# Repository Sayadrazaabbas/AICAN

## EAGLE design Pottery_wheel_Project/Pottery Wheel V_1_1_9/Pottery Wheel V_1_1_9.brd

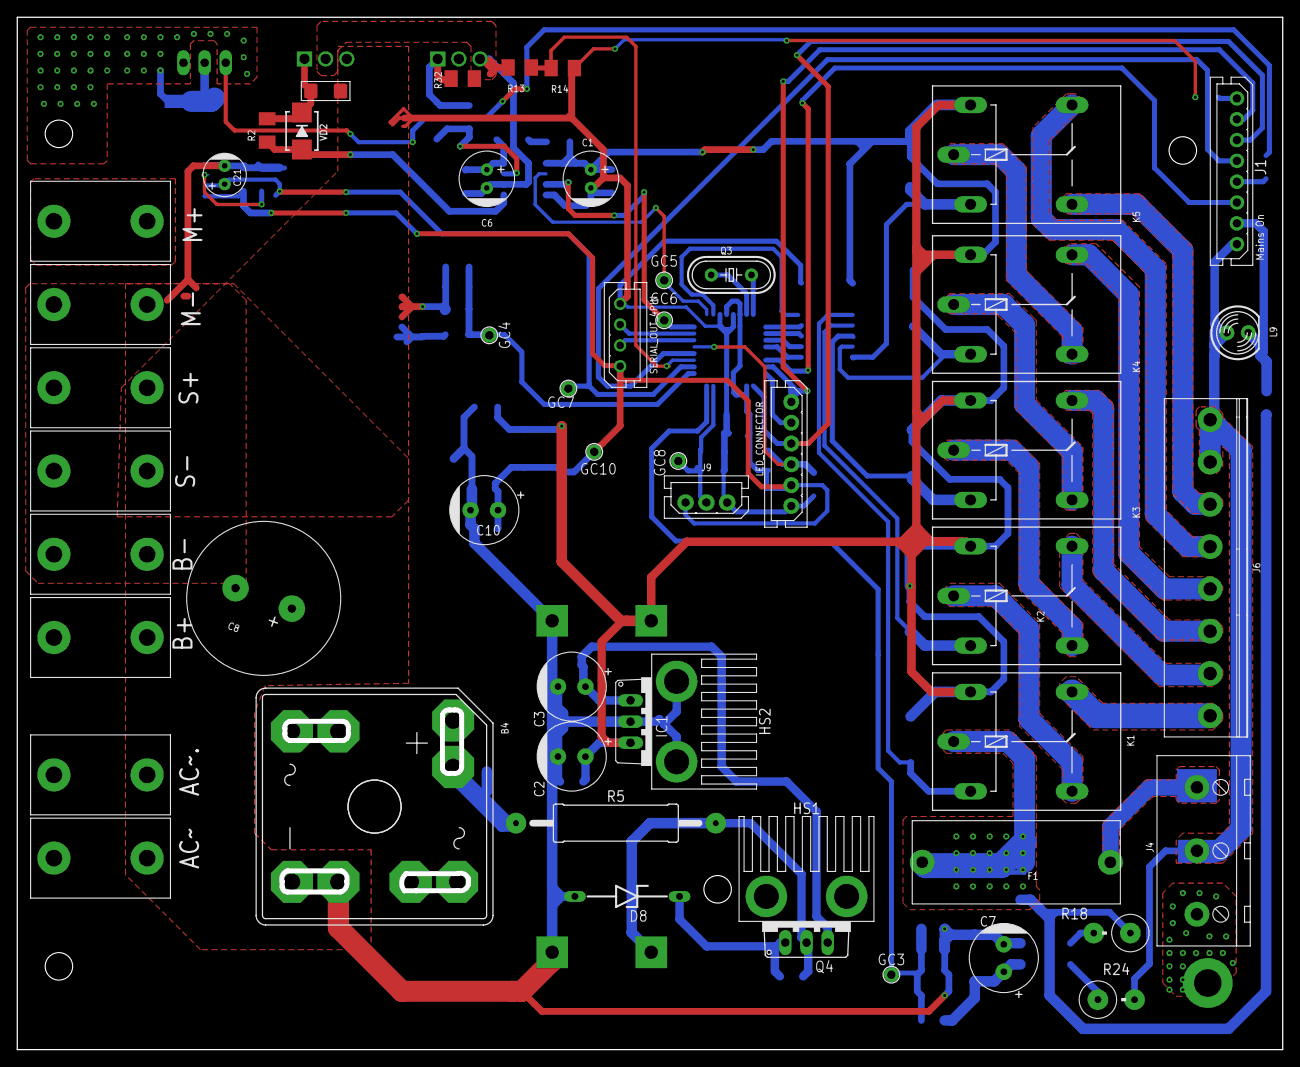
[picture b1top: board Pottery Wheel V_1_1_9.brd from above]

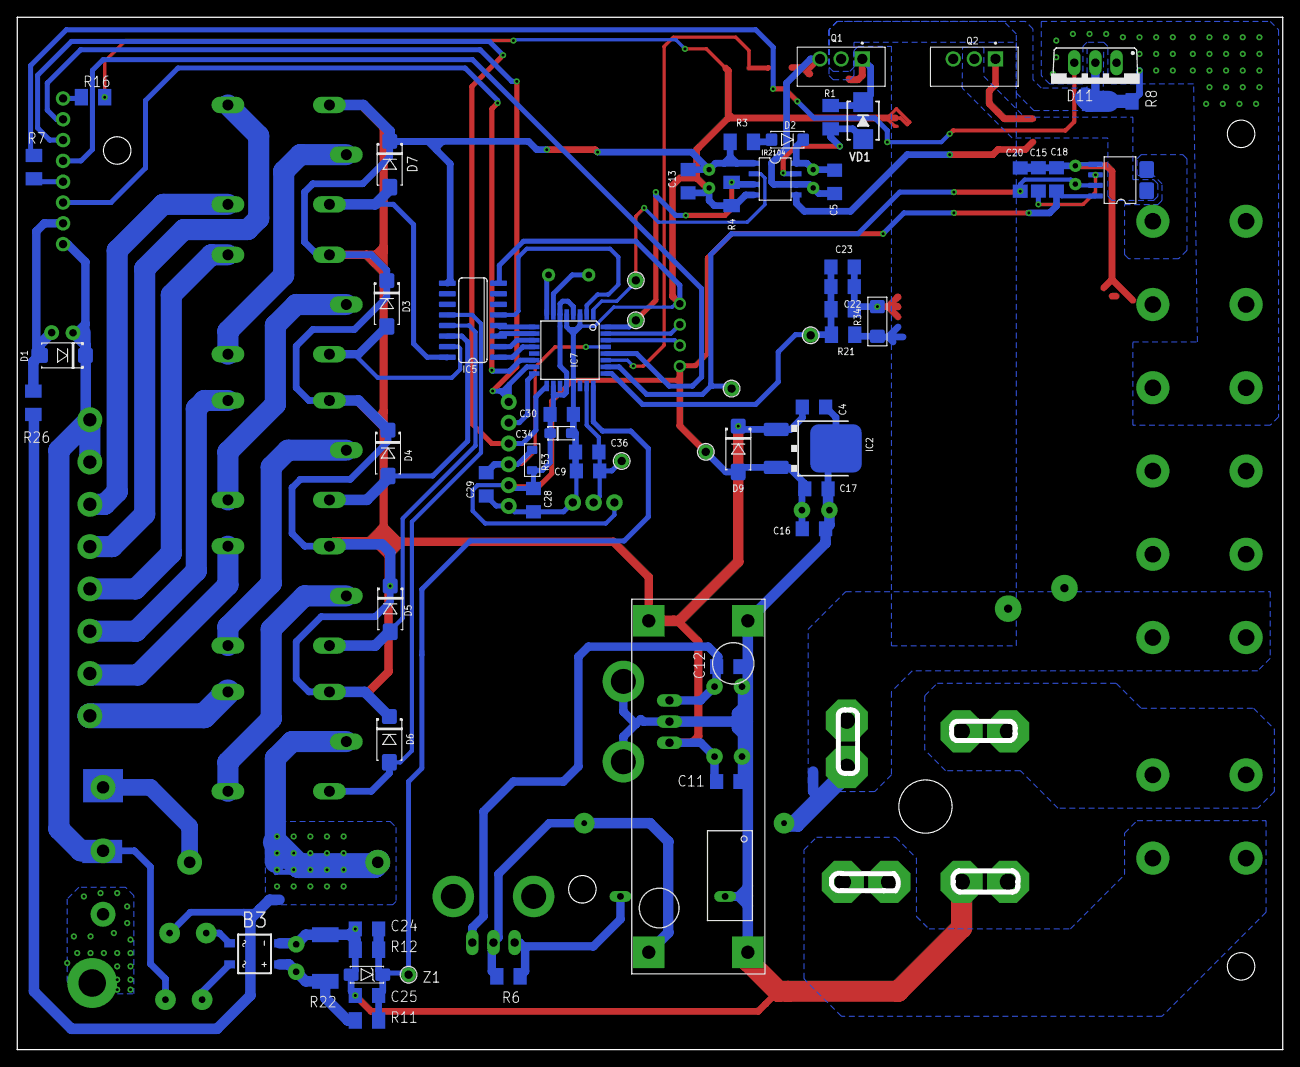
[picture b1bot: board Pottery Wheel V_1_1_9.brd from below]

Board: 2 copper layers, 151.6 x 123.6 mm, 107 parts (55 on the bottom side), 65 nets.

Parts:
AC~, AC~.: 1-PIN_9.6
B3: B1S; MBS
B4: KPC3510; B25A-
B+: 1-PIN_9.6
B-: 1-PIN_9.6
C1, C6: 10uf; C_6_V
C2, C3: DNP; C_8_V
C4, C5, C13, C15, C17, C36: 0.1uf; C1206
C7: 10uf/450v; C_8_V
C8: 4700uf/50V; C_19MM
C9, C16, C18, C20: 1uf; C1206
C10: 10uf/63v; C_8_V
C11, C12: DNP; C1206
C21: 10uf/63v; C_5_V
C22: .1UF; C1206
C23, C25: 1UF; C1206
C24: 0.1UF; C1206
C28, C29, C30: O.1UF; C1206
C34: DNP; TANT_1206
D1, D3, D4, D5, D6, D7, D9: M7; SMB
D2: 5819; SOD-80
D8: DNP; ZDIO12.5
D11: BYV32; TO220ABS
F1: Fuse Holder Pcb Mount; FH_BOX
GC3, GC4, GC5, GC6, GC7, GC8, GC10: P1-17Y
HS1, HS2: DNP; PI-49
IC1: DNP; TO220V
IC2: M7805; DPAK
IC5: ULN2003; SOIC-16
IC7: MEGA8-AI; TQFP32-08
IC8: ACS712-05B; SO-08
J1: MOLEX_8-PIN
J4: 3-PIN_7.62
J6: 5.08 PBT WHITE Power Connecor; 8-PIN_5.08_PWR
J9: 2.54 3 pin JST; MOLEX_3-PIN
K1, K2, K3, K4, K5: G5LE
L9: Red 5mm; LED_5MM
LED_CONNECTOR: MOLEX_6-PIN
M+: 1-PIN_9.6
M-: 1-PIN_9.6
Q1, Q2: IRF2115; TO254P1054X469X2933-3
Q3: 16MHZ; HC49/S
Q4: DNP; TO220AV
R1, R2, R3: 10E; M1206
R4: 10k; M1206
R5: 10E; RES_2W_L
R6: DNP; M1206
R7, R8, R16: 470E; M1206
R11: 1ME; M1206
R12: 11k; M1206
R13: 5.2k; M1206
R14: 1k; M1206
R15: 10K; 1206
R18, R24: 0E; 2W
R21, R32: 10K; M1206
R22: 200K; R2512
R23: 1K; M1206
R26: 100k; M1206
R34: DNP; 1206
R53: 10K; 0805
S+: 1-PIN_9.6
S-: 1-PIN_9.6
SERIAL_OUT_4PIN: MOLEX_4-PIN
U$1: IR2104S
U$3: XL7015
VD1, VD2: M7; SMB
Z1: 4.7V; SMB_Z

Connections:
+5V: C10.+, C16.1, C17.1, C18.1, C28.2, C30.2, C34.+, D9.A, GC10.TP, IC2.3, IC7.4, IC7.6, IC7.18, IC7.20, IC8.8, J9.1, LED_CONNECTOR.2, R53.2, SERIAL_OUT_4PIN.4
+12V: C1.+, C2.+, C4.1, C11.1, C13.1, D3.K, D4.K, D5.K, D6.K, D7.K, D9.K, IC1.3, IC2.1, IC5.9, K1.2, K2.2, K3.2, K4.2, K5.2, R3.2, U$1.1, U$3.OUT+
+24V: B4.+, B4.+1, B+.1, B+.2, C8.1, D11.C, Q1.DRAIN, R5.1, R8.2, R21.1, R34.2
AC_ADC: C24.1, C25.1, GC3.TP, IC7.24, R11.2, R12.1, Z1.K
CURRENT_ADC: C20.1, C21.+, GC7.TP, IC7.26, IC8.7
D4: IC5.5, IC7.2
D5: IC5.4, IC7.9
D6: IC5.3, IC7.10
D7: IC5.2, IC7.11
D8: IC5.1, IC7.12
DC_ADC: C22.1, C23.1, GC4.TP, IC7.25, R21.2, R23.1
GND: B3.-, B4.-, B4.-1, B-.1, B-.2, C1.-, C2.-, C3.-, C4.2, C7.-, C8.2, C9.2, C10.-, C11.2, C12.2, C13.2, C15.2, C16.2, C17.2, C18.2, C20.2, C21.-, C22.2, C23.2, C24.2, C25.2, C28.1, C29.1, C30.1, C34.-, C36.2, D8.A, HS2.1, HS2.2, IC1.2, IC2.4, IC5.8, IC7.3, IC7.5, IC7.21, IC8.5, J9.3, LED_CONNECTOR.1, M-.1, M-.2, Q2.SOURCE, R4.2, R12.2, R14.2, R15.1, R16.2, R22.1, R23.2, R34.1, S-.1, S-.2, SERIAL_OUT_4PIN.1, U$1.4, U$3.IN-, U$3.OUT-, Z1.A
LEDAC_K: D1.A, J1.2, L9.K, R26.2
LIVE: F1.2, K1.P, R18.1, R26.1
LOW_BUS_LED: IC7.14, J1.3
MISO: IC7.16, LED_CONNECTOR.5
MOSI: IC7.15, J1.7, LED_CONNECTOR.6
MOTORADC: IC7.27, R13.2, R14.1
MOTOR_OUT: C5.2, C6.-, IC8.1, IC8.2, Q1.SOURCE, Q2.DRAIN, R13.1, R32.2, U$1.6
unnamed: R1.2, U$1.7, VD1.A
unnamed: R2.2, U$1.5, VD2.A
unnamed: Q2.GAET, R2.1, R15.2, VD2.C
unnamed: Q4.C, R5.2, R6.1, U$3.VIN+
unnamed: AC~.1, AC~.2, B4.AC1, B4.AC1-
unnamed: Q1.GAET, R1.1, R32.1, VD1.C
unnamed: F1.1, J4.3
unnamed: C5.1, C6.+, D2.K, U$1.8
unnamed: D2.A, R3.1
unnamed: C15.1, IC8.6
unnamed: AC~..1, AC~..2, B4.AC2, B4.AC2-
unnamed: J6.1, K1.O
unnamed: K1.S, K2.P
unnamed: J6.2, K2.O
unnamed: K2.S, K3.P
unnamed: K3.S, K4.P
unnamed: J6.3, K3.O
unnamed: J6.4, K4.O
unnamed: D4.A, IC5.14, K3.1
unnamed: C3.+, C12.1, IC1.1, Q4.E
unnamed: D6.A, IC5.12, K1.1
unnamed: J1.4, R7.1
unnamed: D8.C, Q4.B, R6.2
unnamed: D5.A, IC5.13, K2.1
unnamed: IC7.7, Q3.2
unnamed: K4.S, K5.P
unnamed: J6.5, K5.O
unnamed: J6.6, K5.S
unnamed: B3.AC1, R24.1
unnamed: D3.A, IC5.15, K4.1
unnamed: IC7.8, Q3.1
unnamed: D7.A, IC5.16, K5.1
unnamed: B3.AC2, R18.2
unnamed: B3.+, C7.+, R11.1, R22.2
unnamed: IC8.3, IC8.4, M+.1, M+.2
unnamed: J1.8, R16.1
OVRL: IC7.28, J1.5
POT_ADC: C9.1, C36.1, GC8.TP, IC7.23, J9.2
PWM: GC5.TP, IC7.1, U$1.2
RST: C29.2, IC7.29, LED_CONNECTOR.3, R53.1
RXD: IC7.30, SERIAL_OUT_4PIN.3
SCK: IC7.17, J1.6, LED_CONNECTOR.4
SD_PIN: GC6.TP, IC7.32, R4.1, U$1.3
SOLAR_IN: D11.A1, D11.A2, R7.2, R8.1, S+.1, S+.2
TXD: IC7.31, SERIAL_OUT_4PIN.2
VSS: D1.K, J1.1, J4.2, J6.7, J6.8, L9.A, R24.2

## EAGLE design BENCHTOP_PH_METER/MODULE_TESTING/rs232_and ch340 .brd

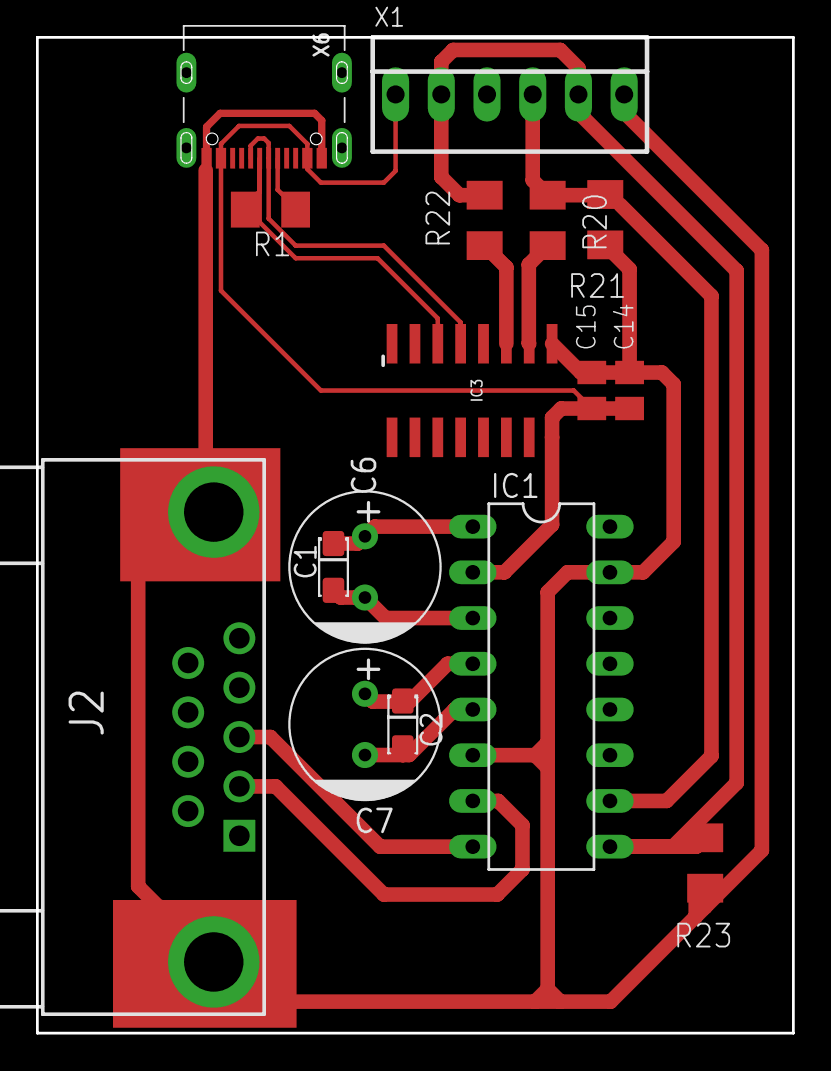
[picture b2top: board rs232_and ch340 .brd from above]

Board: 2 copper layers, 42.0 x 55.3 mm, 16 parts (0 on the bottom side), 14 nets.

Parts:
C1, C2: TANT_1206
C6, C7: CAP_ELE; C_8MM
C14, C15: 1µF; C0805K
IC1: MAX232; DIL16
IC3: CH340G; SOIC16N
J2: DB9'FEMAL'; DB9
R1, R20, R21, R22, R23: M1206
X1: 22-23-2061
X6: USB TYPE C; USB_C_CUSB31-CFM2AX-01-X

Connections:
+5V: C14.2, C15.2, IC1.2, IC3.16, X1.1, X6.A4B9, X6.B4A9
D+: IC3.5, X6.A6, X6.B6
D-: IC3.6, R1.1, R1.2, X6.A7, X6.B7
GND: C14.1, C15.1, IC1.6, IC1.15, IC3.1, J2.G1, J2.G2, R21.1, R23.1, X1.6, X6.A1B12, X6.B1A12
unnamed: IC3.2, R20.2
unnamed: C1.+, C6.1, IC1.1
unnamed: C1.-, C6.2, IC1.3
unnamed: C2.+, C7.1, IC1.4
unnamed: C2.-, C7.2, IC1.5
unnamed: IC1.7, J2.2
unnamed: IC1.8, J2.3
unnamed: IC3.3, R22.2
RX_CH340: IC1.9, R22.1, R23.2, X1.2, X1.5
TX_CH340: IC1.10, R20.1, R21.2, X1.4
